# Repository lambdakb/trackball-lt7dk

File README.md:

# LT7DK PMW3360 Trackball Development Kit

## PCB

|             Front             |            Back             |
| :---------------------------: | :-------------------------: |
| [![PCB Front]][PCB Front PNG] | [![PCB Back]][PCB Back PNG] |

[PCB Front]: output/img/lt7dk-pcb-top.svg
[PCB Front PNG]: output/img/lt7dk-pcb-top.png
[PCB Back]: output/img/lt7dk-pcb-bottom.svg
[PCB Back PNG]: output/img/lt7dk-pcb-bottom.png

The PCB has been designed in [KiCad EDA 9.0](https://www.kicad.org/) using the [`kicad-lkbd`](https://github.com/lambdakb/kicad-lkbd) libraries.

You can preview the project files using [KiCanvas](https://kicanvas.org/?github=https%3A%2F%2Fgithub.com%2Flambdakb%2Ftrackball-lt7dk%2Fblob%2Fmain%2Fpcb%2Flt7dk-pcb.kicad_pro) directly in your browser and download the latest fabrication files for JLCPCB from the [latest release](https://github.com/lambdakb/trackball-lt7dk/releases/latest/).

The exported schematic is also available under [`output/schematics`](output/schematics/).

### PCB Order

| Parameters                       | Value                  |
| -------------------------------- | ---------------------- |
| Base Material                    | FR4                    |
| Layers                           | 2                      |
| Dimensions                       | 62 × 84 mm             |
| PCB Thickness                    | 1.6 mm                 |
| PCB Color [^pcb-color]           | Black                  |
| Silkscreen                       | White                  |
| Surface Finish [^surface-finish] | Lead Free HASL or ENIG |
| Copper Weight                    | 1 oz                   |
| Via Covering                     | Tented                 |
| Min Via Hole Size                | 0.3 mm                 |
| Board Outline Tolerance          | ± 0.2 mm               |

[^pcb-color]: You can select any PCB color you want but some manufacturers such as JLCPCB may charge you more for uncommon combos (such as Blue PCB + ENIG Surface Finish).
[^surface-finish]: The "HASL (with lead)" option is extremely discouraged due to the risk of lead poisoning. We strongly recommend paying the premium for the "Lead Free HASL" option.

### JLCPCB Specific Options

<!-- NOTE: This is generic and used for ALL LambdaKB PCBs EXCEPT for cases PCB   -->

#### Mark on PCB

The following JCLPCB specific options are used to serialize PCBs on order. An 8 × 8 mm silkscreen square was added to the PCB to allow for a 2D barcode to be added.

| Parameters            | Value                       |
| --------------------- | --------------------------- |
| Mark on PCB           | 2D barcode (Serial Number)  |
| - Printing            | 2D barcode & Number         |
| - Code Type           | Data Matrix Code            |
| - Prefix              | `LKBD_LT7DK_v100`           |
| - Unique Number       | Remove                      |
| - Incrementing Number | _`YYMM01`_ (e.g.: `250300`) |
| - 2D Barcode Size     | 8 × 8 mm                    |
| - 2D Barcode Position | Specify Position            |

Serial numbers are based on the current date using the `YYMM01` format for its incrementing numbers. Orders in February 2025 would start then start it at `250300`, making the final serial `LKBD_LT7DK_v100_250300`.

## BOM

| Part                          | Ref.                                                          | Quantity | Optional | Remarks                                                                                                                                                          |
| ----------------------------- | ------------------------------------------------------------- | :------: | :------: | ---------------------------------------------------------------------------------------------------------------------------------------------------------------- |
| PCB                           | [LT7DK PCB](./README.md#pcb)                                  |    1     |    ❌    | See [PCB](./README.md#pcb) section on how to order it.                                                                                                           |
| Pro Micro Controller          | [Arduino Pro Micro 5V], [Adafruit KB2040] or [nice!nano]      |    1     |    ❌    | Supports various Pro Micro style controller (including RP2040 based ones) as well as the nice!nano for wireless builds. [^wireless]                              |
| MCU Socket                    | [DIP-24 Round Socket (Wide, 15.24 mm)]                        |    1     |    ✅    | Recommended to socket the controller, can be omitted if soldered directly. Compatibles pins are required such as dismantled [LED strip male adapters].           |
| Reset Push Button             | [DIP 2pin Momentary Push Button (6 × 3.5 mm)]                 |    1     |    ✅    | Used as a reset switch, can be omitted if you flash the controller before installing it or if the controller can be put in bootloader mode from any other means. |
| Micro Switches                | [D2FC-F-7N Micro Switch] or compatible                        |   4-7    |    ❌    | Micro switches for mouse buttons, you do not have to populate all of them depending on how you intend to use the PCB.                                            |
| PMW3360 Optical Sensor & Lens | [PMW3360DM-T2QU + LM19-LSI]                                   |    1     |    ❌    | Optical mouse sensor and lens used to detect trackball movement.                                                                                                 |
| 1.8V DO                       | [TPS76318 Fixed 1.8V LDO (SOT-23-5)]                          |    1     |    ❌    | Power regulator for optical sensor.                                                                                                                              |
| 1uF Capacitor                 | [0805 SMD Ceramic Capacitor]                                  |    1     |    ❌    | Required by the optical sensor LDO.                                                                                                                              |
| 4.7uF Capacitors              | [0805 SMD Ceramic Capacitor]                                  |    2     |    ❌    | Power filtering capacitor for optical sensor and required LDO.                                                                                                   |
| 100nF Capacitors              | [0805 SMD Ceramic Capacitor]                                  |   1-2    |    ❌    | One if required for the power filtering of the optical sensor, the second one is only required if installing the NeoPixel RGB LED.                               |
| 10K Ω Resistor                | [0805 SMD Resistor]                                           |    1     |    ❌    | Required by the optical sensor.                                                                                                                                  |
| 39 Ω Resistor                 | [0805 SMD Resistor]                                           |    1     |    ❌    | Required by the optical sensor.                                                                                                                                  |
| 0.91" OLED Display            | [SSD1306 0.91" 128X32 OLED I²C Display Module]                |   0-1    |    ✅    | Optional, not recommended for wireless builds. [^wireless]                                                                                                       |
| NeoPixel RGB LED              | [WS2812B 5050 SMD RGB LED] or [SK6812 5050 SMD RGBW LED]      |   0-1    |    ✅    | Optional, MUST NOT be placed on wireless builds as 5V output is not provided on the RAW pin by the controller. [^wireless]                                       |
| Power Slide Switch            | [PCM12SMTR] or [MSK-12C02]                                    |    1     |    ✅    | Only required for battery powered wireless builds. [^wireless]                                                                                                   |
| Battery Connector             | [JST-PH 2pin right-angle Male Connector]                      |    1     |    ✅    | Only needed for battery powered wireless builds if the battery is not soldered directly to the board (recommended). [^wireless]                                  |
| 3.7V Li-Po Battery            | [603449 (1100 mAh)] or [503450 (1000 mAh)] 3.7V Li-Po Battery |    1     |    ✅    | Only required for battery powered wireless builds, any 3.7 V (1 Cell) Li-Po battery slimmer than 8 mm with a JST-PH connector should work. [^wireless]           |

[Arduino Pro Micro 5V]: https://www.sparkfun.com/pro-micro-5v-16mhz.html
[Adafruit KB2040]: https://www.adafruit.com/product/5302
[nice!nano]: https://nicekeyboards.com/nice-nano/
[DIP-24 Round Socket (Wide, 15.24 mm)]: https://www.aliexpress.com/item/1005005770166098.html
[LED strip male adapters]: (https://www.aliexpress.com/item/1005005742644313.html)
[DIP 2pin Momentary Push Button (6 × 3.5 mm)]: https://www.aliexpress.com/item/1005001849576755.html
[D2FC-F-7N Micro Switch]: https://www.aliexpress.com/item/1005005018374123.html
[PMW3360DM-T2QU + LM19-LSI]: https://www.aliexpress.com/item/4000904265601.html?
[TPS76318 Fixed 1.8V LDO (SOT-23-5)]: https://www.aliexpress.com/item/1005007852956393.html
[0805 SMD Ceramic Capacitor]: https://www.aliexpress.com/item/32812155708.html
[0805 SMD Resistor]: https://www.aliexpress.com/item/32847143167.html
[WS2812B 5050 SMD RGB LED]: https://www.aliexpress.com/item/4001345875756.html
[SK6812 5050 SMD RGBW LED]: https://www.aliexpress.com/item/32666691387.html
[SSD1306 0.91" 128X32 OLED I²C Display Module]: https://www.aliexpress.com/item/32777216785.html
[PCM12SMTR]: https://www.digikey.com/en/products/detail/c-k/PCM12SMTR/1640112
[MSK-12C02]: https://www.aliexpress.com/item/4000685483225.html
[JST-PH 2pin right-angle Male Connector]: https://www.aliexpress.com/item/1005004955655144.html
[603449 (1100 mAh)]: https://amzn.eu/d/e3uVbqB
[503450 (1000 mAh)]: https://aliexpress.com/item/1005003198563309.html

[^wireless]: See [Wireless Support](./README.md#wireless-support) for more details.

## Firmware

Firmware has been built using the [`vial` fork](https://github.com/vial-kb/vial-qmk) of [QMK](https://qmk.fm).

## Wireless Support

To add wireless support to this keyboard, you will need a controller that provides power input and a charging circuit between the top RAW and GND such as the `nice!nano`.

The PCB itself provides a way to attach a JST-PH connector as well as a slide switch for power management. This slide switch must be set to ON for the charging circuit to work.

This hasn't been extensively tested yet and should be considered experimental (no wireless firmware will be provided for now). The feature was added to the PCB as way for us to prototype a potential wireless keyboard.

## References

### Inspiration

- [aki27kbd trackball_module](https://github.com/aki27kbd/trackball_module)
- [Ploopy Nano Trackball](https://ploopy.co/nano-trackball/) ([source](https://github.com/ploopyco/nano-trackball))
- [Ploopy Adept Trackball](https://ploopy.co/adept-trackball/) ([source](https://github.com/ploopyco/adept-trackball))
- [jfedor2 DIY trackball with scroll ring](https://github.com/jfedor2/scroll-ring-trackball)
- [The Orb trackball](https://github.com/dpapavas/orb-trackball)
- [brickbots aball](https://github.com/brickbots/aball)

### PCB Designs

- [jfedor2 PMW3360 Breakout Board](https://github.com/jfedor2/pmw3360-breakout)
- [jfedor2 PMW3360+RP2040](https://github.com/jfedor2/rp2040-pmw3360)
- [asav.dev PMW3360 Module](https://asav.dev/pmw3360/)
- [SideraKB PMW3360 PCB](https://github.com/siderakb/pmw3360-pcb)
- [protieusz Omega-Petit](https://github.com/protieusz/Omega-Petit)

## License

This design is licensed under the [CERN Open Hardware Licence Version 2 – Strongly Reciprocal (CERN-OHL-S-2.0)](https://opensource.org/license/cern-ohl-s).

You are free to use, modify, and distribute this design for any purpose, provided that:

- **Attribution**: Appropriate credit is given, a link to the license is provided, and any modifications are clearly indicated.
- **Reciprocity**: Any derivative works must be released under the same license.

If you are a retailer or business interested in producing or selling this design or related products, I’d love to discuss it! Please feel free to reach out so we can explore potential arrangements.

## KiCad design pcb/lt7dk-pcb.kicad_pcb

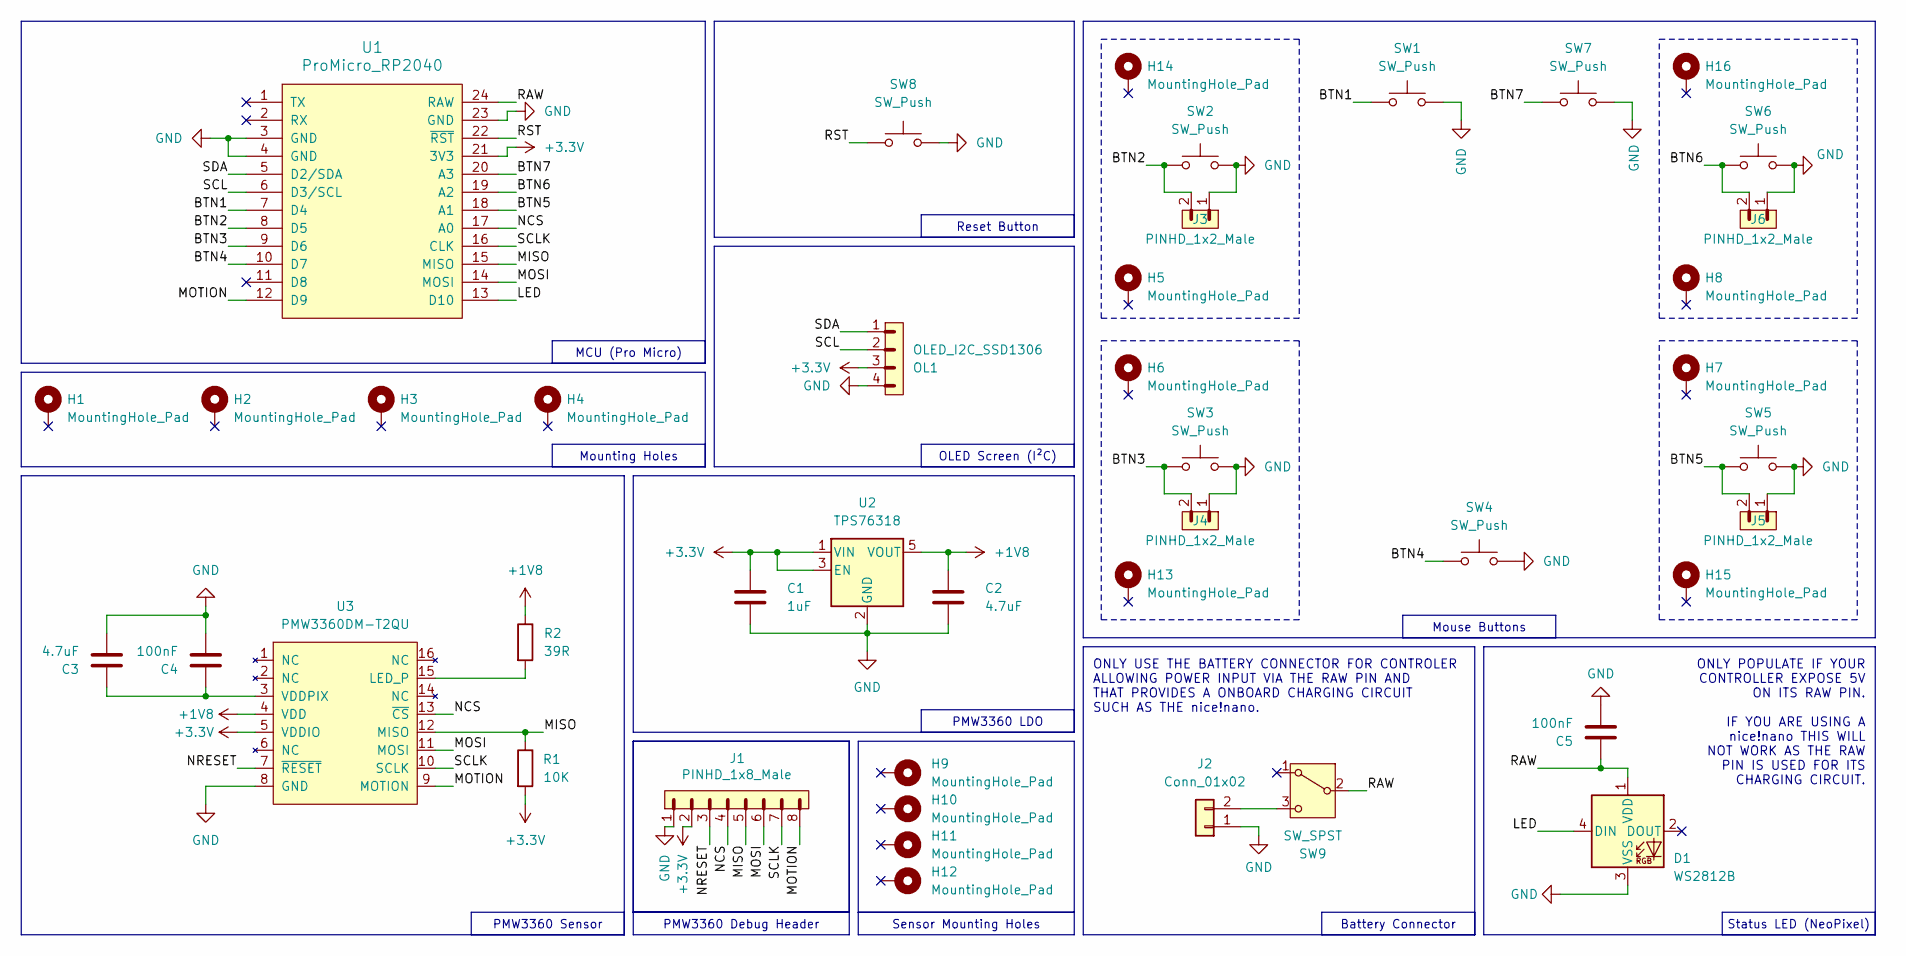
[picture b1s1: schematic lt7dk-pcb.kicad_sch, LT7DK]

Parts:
C1: 1uF; C_0805_2012Metric_Pad1.18x1.45mm_HandSolder; JLC 0805
C2, C3: 4.7uF; C_0805_2012Metric_Pad1.18x1.45mm_HandSolder; JLC 0805
C4, C5: 100nF; C_0805_2012Metric_Pad1.18x1.45mm_HandSolder; JLC 0805
D1: WS2812B; LED_WS2812B_PLCC4_5.0x5.0mm_P3.2mm
H1, H2, H3, H4, H5, H6, H7, H8, H9, H10, H11, H12, H13, H14, H15, H16: MountingHole_Pad; MountingHole_2.2mm_M2_ISO14580_Pad
J1: PINHD_1x8_Male; PinHeader_1x08_P2.54mm_Vertical
J2: Conn_01x02; JST_PH_S2B-PH-K_1x02_P2.00mm_Horizontal
J3, J4, J5, J6: PINHD_1x2_Male; PinHeader_1x02_P2.54mm_Vertical
OL1: OLED_I2C_SSD1306; OLED_SSD1306_128x32_0.91inch_I2C_btmSilk
R1: 10K; R_0805_2012Metric_Pad1.20x1.40mm_HandSolder; JLC 0805
R2: 39R; R_0805_2012Metric_Pad1.20x1.40mm_HandSolder; JLC 0805
SW1, SW2, SW3, SW4, SW5, SW6, SW7: SW_Push; SW_D2FC_OMR
SW8: SW_Push; SW_Push_1P1T_6x3.5mm
SW9: SW_SPST; SW_SPDT_PCM12; LCSC C221841
U1: ProMicro_RP2040; MCU_KB2040_DIP-24_Socket_Reverse
U2: TPS76318; SOT-23-5; JLC SOT-23-5
U3: PMW3360DM-T2QU; JLC DIP-16

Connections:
+1V8: C2.2, R2.1, U2.5 (VOUT), U3.4 (VDD)
+3.3V: C1.2, J1.2, OL1.3, R1.2, U1.21 (3V3), U2.1 (VIN), U2.3 (EN), U3.5 (VDDIO)
/BTN1: SW1.1, U1.7 (D4)
/BTN2: J3.2, SW2.1, U1.8 (D5)
/BTN3: J4.2, SW3.1, U1.9 (D6)
/BTN4: SW4.1, U1.10 (D7)
/BTN5: J5.2, SW5.1, U1.18 (A1)
/BTN6: J6.2, SW6.1, U1.19 (A2)
/BTN7: SW7.1, U1.20 (A3)
/LED: D1.4 (DIN), U1.13 (D10)
/MISO: J1.5, R1.1, U1.15 (MISO), U3.12 (MISO)
/MOSI: J1.6, U1.14 (MOSI), U3.11 (MOSI)
/MOTION: J1.8, U1.12 (D9), U3.9 (MOTION)
/NCS: J1.4, U1.17 (A0), U3.13 (~CS)
/NRESET: J1.3, U3.7 (~RESET)
/RAW: C5.2, D1.1 (VDD), SW9.2 (B), U1.24 (RAW)
/RST: SW8.1, U1.22 (~RST)
/SCL: OL1.2, U1.6 (D3/SCL)
/SCLK: J1.7, U1.16 (CLK), U3.10 (SCLK)
/SDA: OL1.1, U1.5 (D2/SDA)
GND: C1.1, C2.1, C3.1, C4.1, C5.1, D1.3 (VSS), J1.1, J2.1, J3.1, J4.1, J5.1, J6.1, OL1.4, SW1.2, SW2.2, SW3.2, SW4.2, SW5.2, SW6.2, SW7.2, SW8.2, U1.3 (GND), U1.4 (GND), U1.23 (GND), U2.2 (GND), U3.8 (GND)
unnamed: J2.2, SW9.3 (C)
unnamed: R2.2, U3.15 (LED_P)
unnamed: C3.2, C4.2, U3.3 (VDDPIX)

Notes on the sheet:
ONLY USE THE BATTERY CONNECTOR FOR CONTROLER ALLOWING POWER INPUT VIA THE RAW PIN AND THAT PROVIDES A ONBOARD CHARGING CIRCUIT SUCH AS THE nice!nano.
ONLY POPULATE IF YOUR CONTROLLER EXPOSE 5V ON ITS RAW PIN. IF YOU ARE USING A nice!nano THIS WILL NOT WORK AS THE RAW PIN IS USED FOR ITS CHARGING CIRCUIT.
Mounting Holes
PMW3360 Sensor
Reset Button
PMW3360 Debug Header
MCU (Pro Micro)
OLED Screen (I²C)
Status LED (NeoPixel)
Mouse Buttons
Battery Connector
PMW3360 LDO
Sensor Mounting Holes

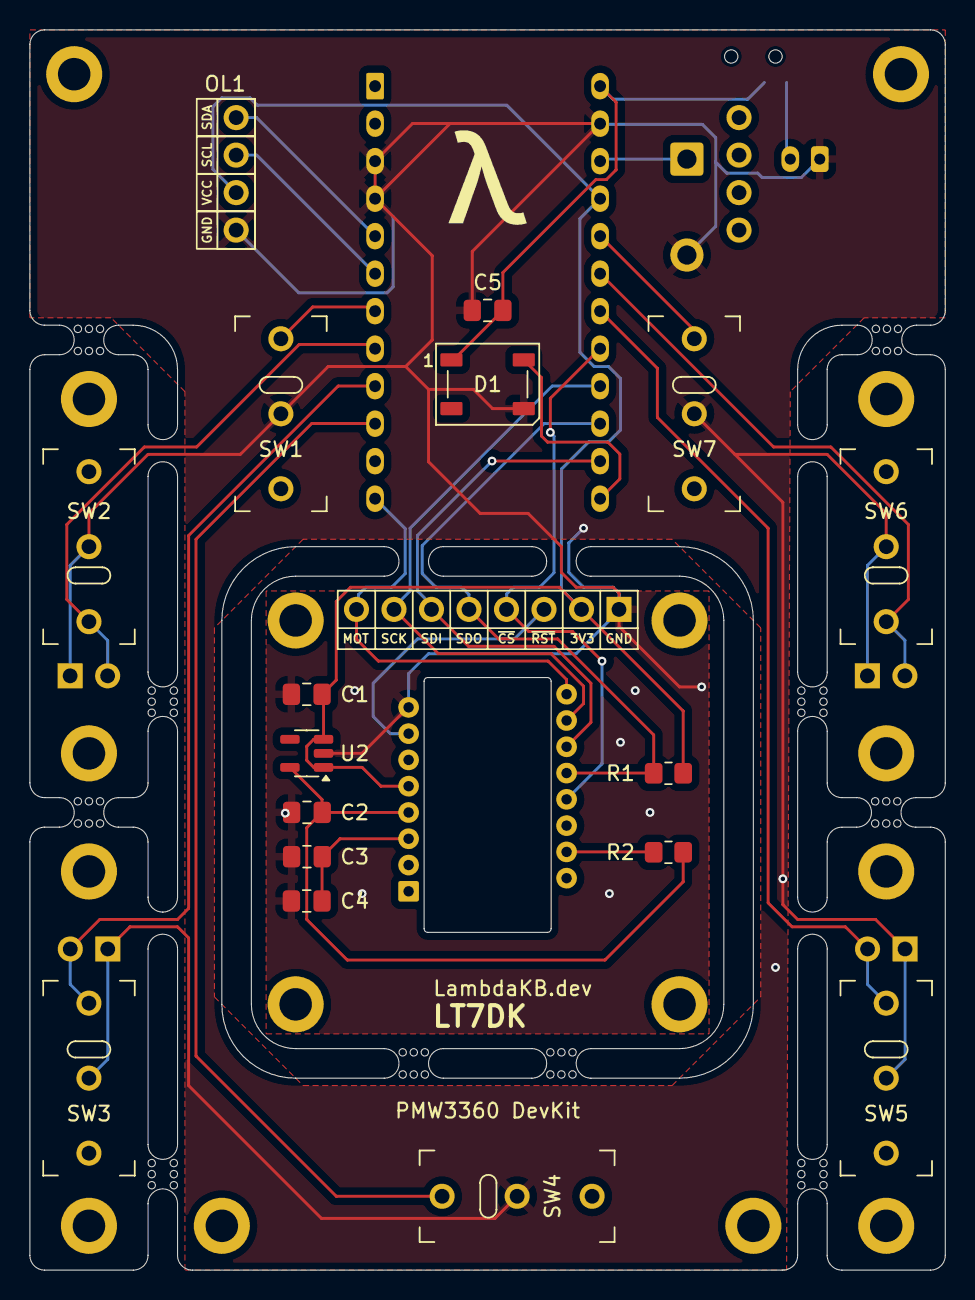
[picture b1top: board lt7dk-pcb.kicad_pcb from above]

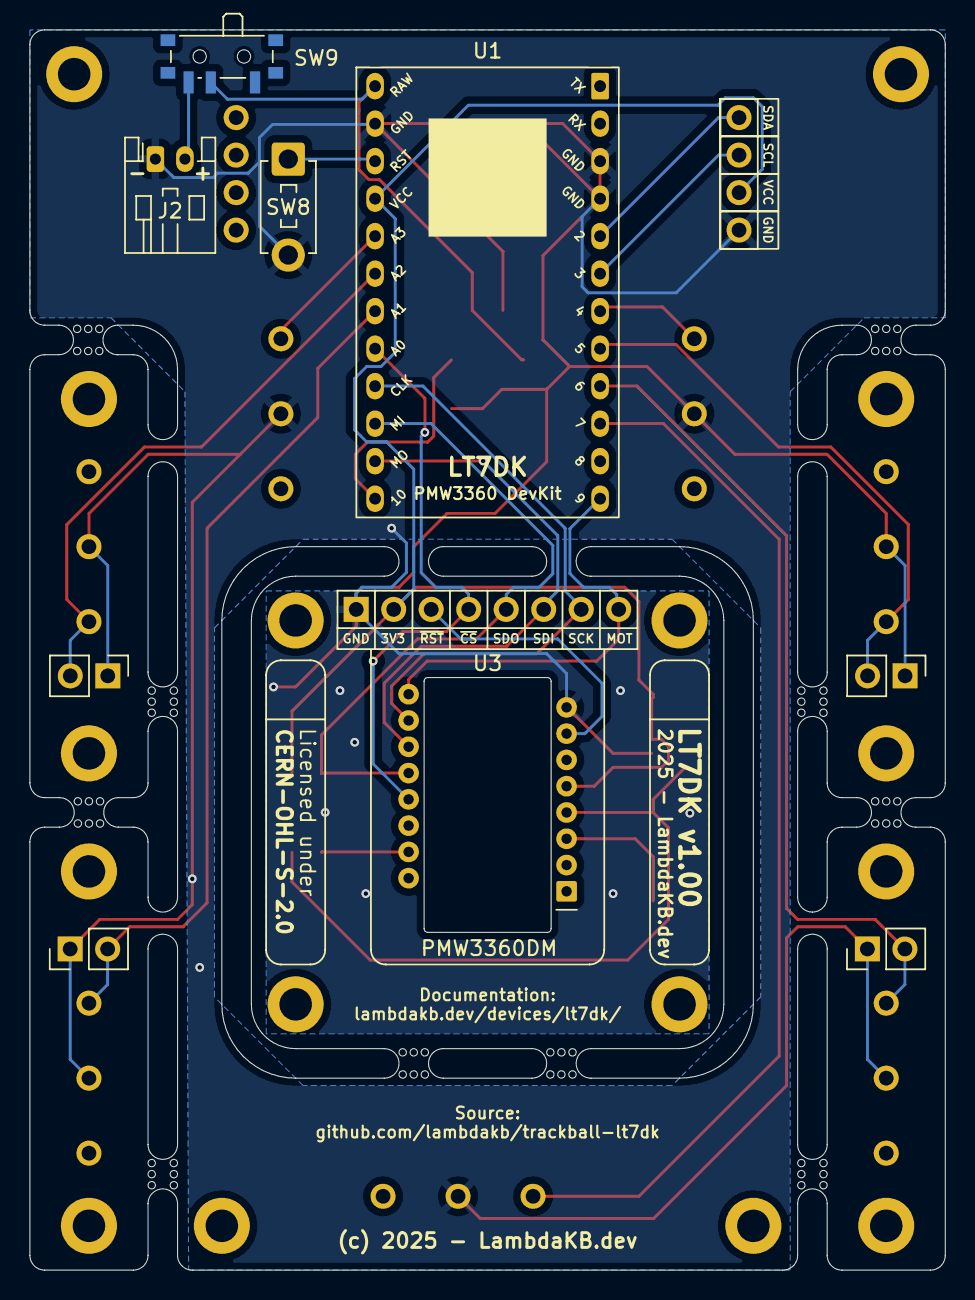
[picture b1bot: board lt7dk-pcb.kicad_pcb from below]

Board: 2 copper layers, 62.0 x 84.0 mm, 54 parts (10 on the bottom side), 24 nets.

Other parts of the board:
J7: PINHD_1x4_Female; PinSocket_1x04_P2.54mm_Vertical
MouseBite_2mm_Slot, MouseBite_2mm_Slot#2, MouseBite_2mm_Slot#3, MouseBite_2mm_Slot#4, MouseBite_2mm_Slot#5, MouseBite_2mm_Slot#6, MouseBite_2mm_Slot#7, MouseBite_2mm_Slot#8, MouseBite_2mm_Slot#9, MouseBite_2mm_Slot#10: VAL**; MouseBite_2mm_Slot

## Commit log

2025-01-24 Init repository
2025-01-29 First draft of PMW3360 Trackball DevKit
2025-02-03 Update mouse bites & add some silkscreen info
2025-02-03 Add used assets
2025-02-04 Update front silkscreen & fix export
2025-02-04 Cleanup schematic and pcb
2025-02-06 Add BOM to README.md
2025-02-07 Add BOM to README.md (#1)
2025-02-07 Add more info to back silkscreen
2025-02-07 Add PCB order instruction + PTH to add a support for the OLED screen
2025-02-07 Add PCB order instruction + PTH to add a support for the OLED screen (#2)
2025-02-09 Fix README links
2025-04-12 Upgrade project to KiCad 9
2025-04-12 Upgrade project to KiCad 9 (#3)
2025-05-13 Update gitattributes

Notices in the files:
README.md:
License: CERN-OHL-S-2.0
pcb/lt7dk-pcb.kicad_pcb:
(c) 2025 - LambdaKB.dev
